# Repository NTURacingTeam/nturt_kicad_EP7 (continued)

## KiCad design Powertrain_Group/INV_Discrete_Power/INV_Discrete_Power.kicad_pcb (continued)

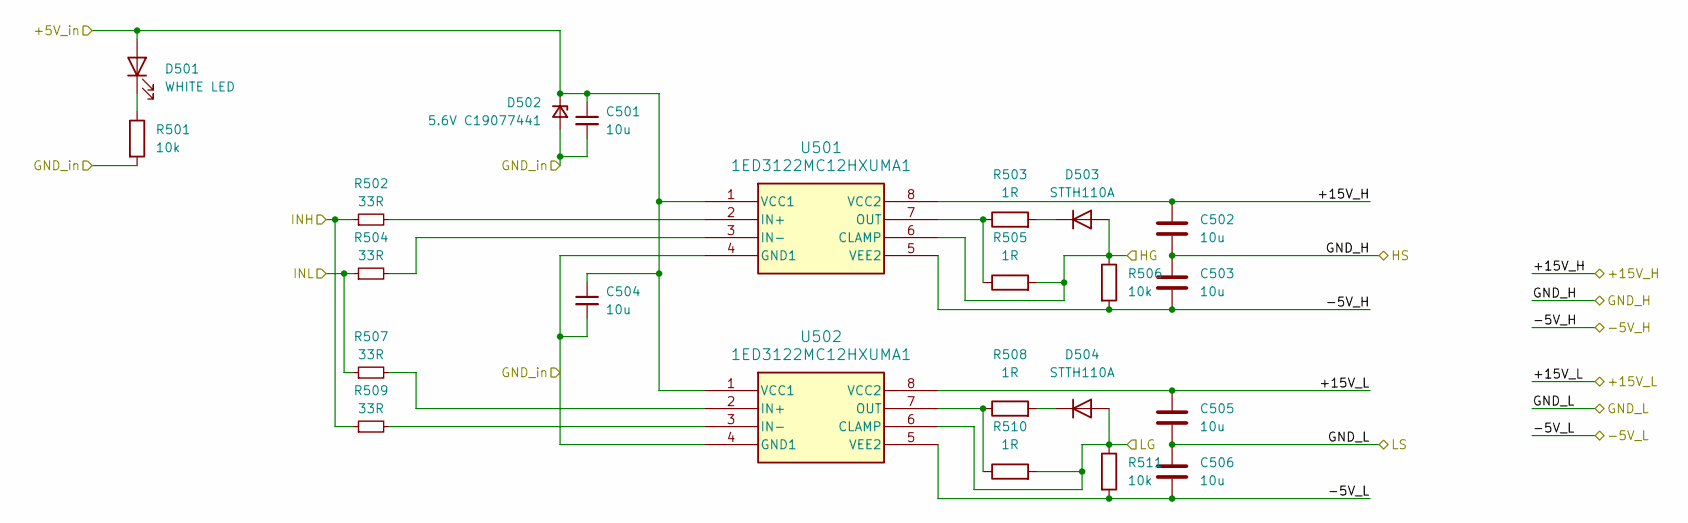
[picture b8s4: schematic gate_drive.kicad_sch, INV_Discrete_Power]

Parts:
C501, C502, C503, C504, C505, C506: 10u; C_0805_2012Metric
D501: WHITE LED; LED_0603_1608Metric
D502: 5.6V C19077441; D_SOD-323
D503, D504: STTH110A; D_SMA
R501: 10k; R_0402_1005Metric
R502, R504, R507, R509: 33R; R_0402_1005Metric
R503, R505, R508, R510: 1R; R_1206_3216Metric
R506, R511: 10k; R_0603_1608Metric
U501, U502: 1ED3122MC12HXUMA1; Infineon_PG-DSO-8-59_7.5x6.3mm

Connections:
/phaseW/PWR_+5V: C501.1, C504.1, D501.2 (A), D502.1 (K), U501.1 (VCC1), U502.1 (VCC1); also elsewhere on the board
/phaseW/PWR_GND: C501.2, C504.2, D502.2 (A), R501.2, U501.4 (GND1), U502.4 (GND1); also elsewhere on the board
/phaseW/gate_drive/+15V_H: C502.1, U501.8 (VCC2); also elsewhere on the board
/phaseW/gate_drive/+15V_L: C505.1, U502.8 (VCC2); also elsewhere on the board
/phaseW/gate_drive/-5V_H: C503.2, R506.2, U501.5 (VEE2); also elsewhere on the board
/phaseW/gate_drive/-5V_L: C506.2, R511.2, U502.5 (VEE2); also elsewhere on the board
/phaseW/gate_drive/GND_H: C502.2, C503.1; also elsewhere on the board
/phaseW/gate_drive/GND_L: C505.2, C506.1; also elsewhere on the board
/phaseW/gate_drive/HG: D503.2 (A), R505.2, R506.1, U501.6 (CLAMP); also elsewhere on the board
/phaseW/gate_drive/INH: R502.1, R509.1; also elsewhere on the board
/phaseW/gate_drive/INL: R504.1, R507.1; also elsewhere on the board
/phaseW/gate_drive/LG: D504.2 (A), R510.2, R511.1, U502.6 (CLAMP); also elsewhere on the board
unnamed: D501.1 (K), R501.1
unnamed: D503.1 (K), R503.2
unnamed: D504.1 (K), R508.2
unnamed: R502.2, U501.2 (IN+)
unnamed: R504.2, U501.3 (IN-)
unnamed: R503.1, R505.1, U501.7 (OUT)
unnamed: R507.2, U502.2 (IN+)
unnamed: R509.2, U502.3 (IN-)
unnamed: R508.1, R510.1, U502.7 (OUT)

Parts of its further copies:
C701, C702, C703, C704, C705, C706, C901, C902, C903, C904, C905, C906: 10u; C_0805_2012Metric
D701, D901: WHITE LED; LED_0603_1608Metric
D702, D902: 5.6V C19077441; D_SOD-323
D703, D704, D903, D904: STTH110A; D_SMA
R701, R901: 10k; R_0402_1005Metric
R702, R704, R707, R709, R902, R904, R907, R909: 33R; R_0402_1005Metric
R703, R705, R708, R710, R903, R905, R908, R910: 1R; R_1206_3216Metric
R706, R711, R906, R911: 10k; R_0603_1608Metric
U701, U702, U901, U902: 1ED3122MC12HXUMA1; Infineon_PG-DSO-8-59_7.5x6.3mm

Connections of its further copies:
/phaseU/PWR_+5V: C901.1, C904.1, D901.2 (A), D902.1 (K), U901.1 (VCC1), U902.1 (VCC1); also elsewhere on the board
/phaseU/PWR_GND: C901.2, C904.2, D902.2 (A), R901.2, U901.4 (GND1), U902.4 (GND1); also elsewhere on the board
/phaseU/gate_drive/+15V_H: C902.1, U901.8 (VCC2); also elsewhere on the board
/phaseU/gate_drive/+15V_L: C905.1, U902.8 (VCC2); also elsewhere on the board
/phaseU/gate_drive/-5V_H: C903.2, R906.2, U901.5 (VEE2); also elsewhere on the board
/phaseU/gate_drive/-5V_L: C906.2, R911.2, U902.5 (VEE2); also elsewhere on the board
/phaseU/gate_drive/GND_H: C902.2, C903.1; also elsewhere on the board
/phaseU/gate_drive/GND_L: C905.2, C906.1; also elsewhere on the board
/phaseU/gate_drive/HG: D903.2 (A), R905.2, R906.1, U901.6 (CLAMP); also elsewhere on the board
/phaseU/gate_drive/INH: R902.1, R909.1; also elsewhere on the board
/phaseU/gate_drive/INL: R904.1, R907.1; also elsewhere on the board
/phaseU/gate_drive/LG: D904.2 (A), R910.2, R911.1, U902.6 (CLAMP); also elsewhere on the board
/phaseV/PWR_+5V: C701.1, C704.1, D701.2 (A), D702.1 (K), U701.1 (VCC1), U702.1 (VCC1); also elsewhere on the board
/phaseV/PWR_GND: C701.2, C704.2, D702.2 (A), R701.2, U701.4 (GND1), U702.4 (GND1); also elsewhere on the board
/phaseV/gate_drive/+15V_H: C702.1, U701.8 (VCC2); also elsewhere on the board
/phaseV/gate_drive/+15V_L: C705.1, U702.8 (VCC2); also elsewhere on the board
/phaseV/gate_drive/-5V_H: C703.2, R706.2, U701.5 (VEE2); also elsewhere on the board
/phaseV/gate_drive/-5V_L: C706.2, R711.2, U702.5 (VEE2); also elsewhere on the board
/phaseV/gate_drive/GND_H: C702.2, C703.1; also elsewhere on the board
/phaseV/gate_drive/GND_L: C705.2, C706.1; also elsewhere on the board
/phaseV/gate_drive/HG: D703.2 (A), R705.2, R706.1, U701.6 (CLAMP); also elsewhere on the board
/phaseV/gate_drive/INH: R702.1, R709.1; also elsewhere on the board
/phaseV/gate_drive/INL: R704.1, R707.1; also elsewhere on the board
/phaseV/gate_drive/LG: D704.2 (A), R710.2, R711.1, U702.6 (CLAMP); also elsewhere on the board
unnamed: D701.1 (K), R701.1
unnamed: D703.1 (K), R703.2
unnamed: D704.1 (K), R708.2
unnamed: D901.1 (K), R901.1
unnamed: D903.1 (K), R903.2
unnamed: D904.1 (K), R908.2
unnamed: R702.2, U701.2 (IN+)
unnamed: R704.2, U701.3 (IN-)
unnamed: R703.1, R705.1, U701.7 (OUT)
unnamed: R707.2, U702.2 (IN+)
unnamed: R709.2, U702.3 (IN-)
unnamed: R708.1, R710.1, U702.7 (OUT)
unnamed: R902.2, U901.2 (IN+)
unnamed: R904.2, U901.3 (IN-)
unnamed: R903.1, R905.1, U901.7 (OUT)
unnamed: R907.2, U902.2 (IN+)
unnamed: R909.2, U902.3 (IN-)
unnamed: R908.1, R910.1, U902.7 (OUT)

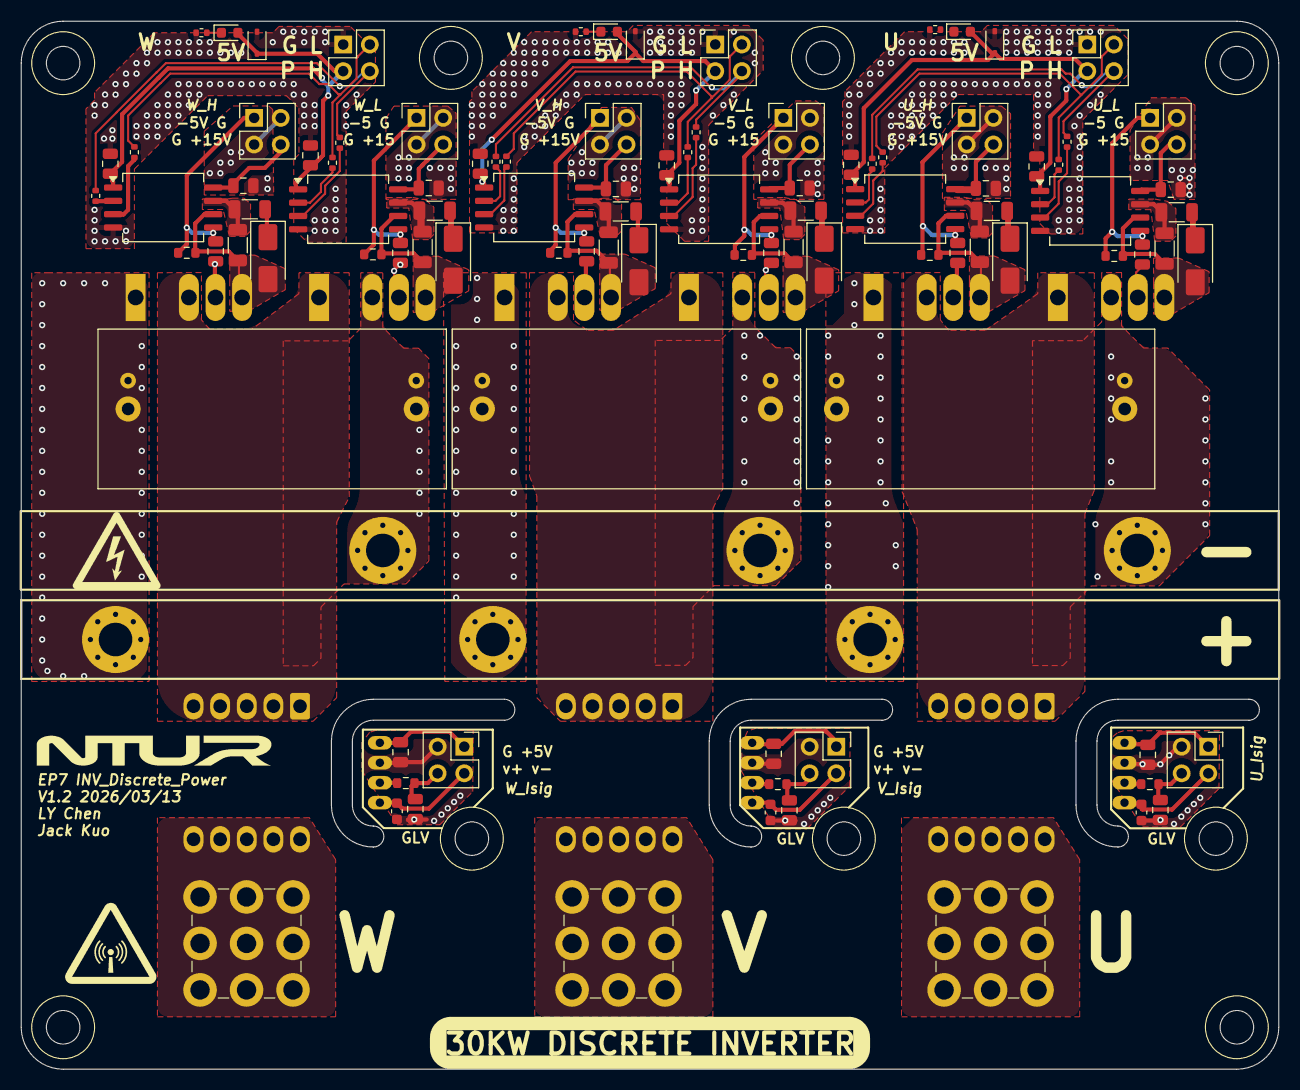
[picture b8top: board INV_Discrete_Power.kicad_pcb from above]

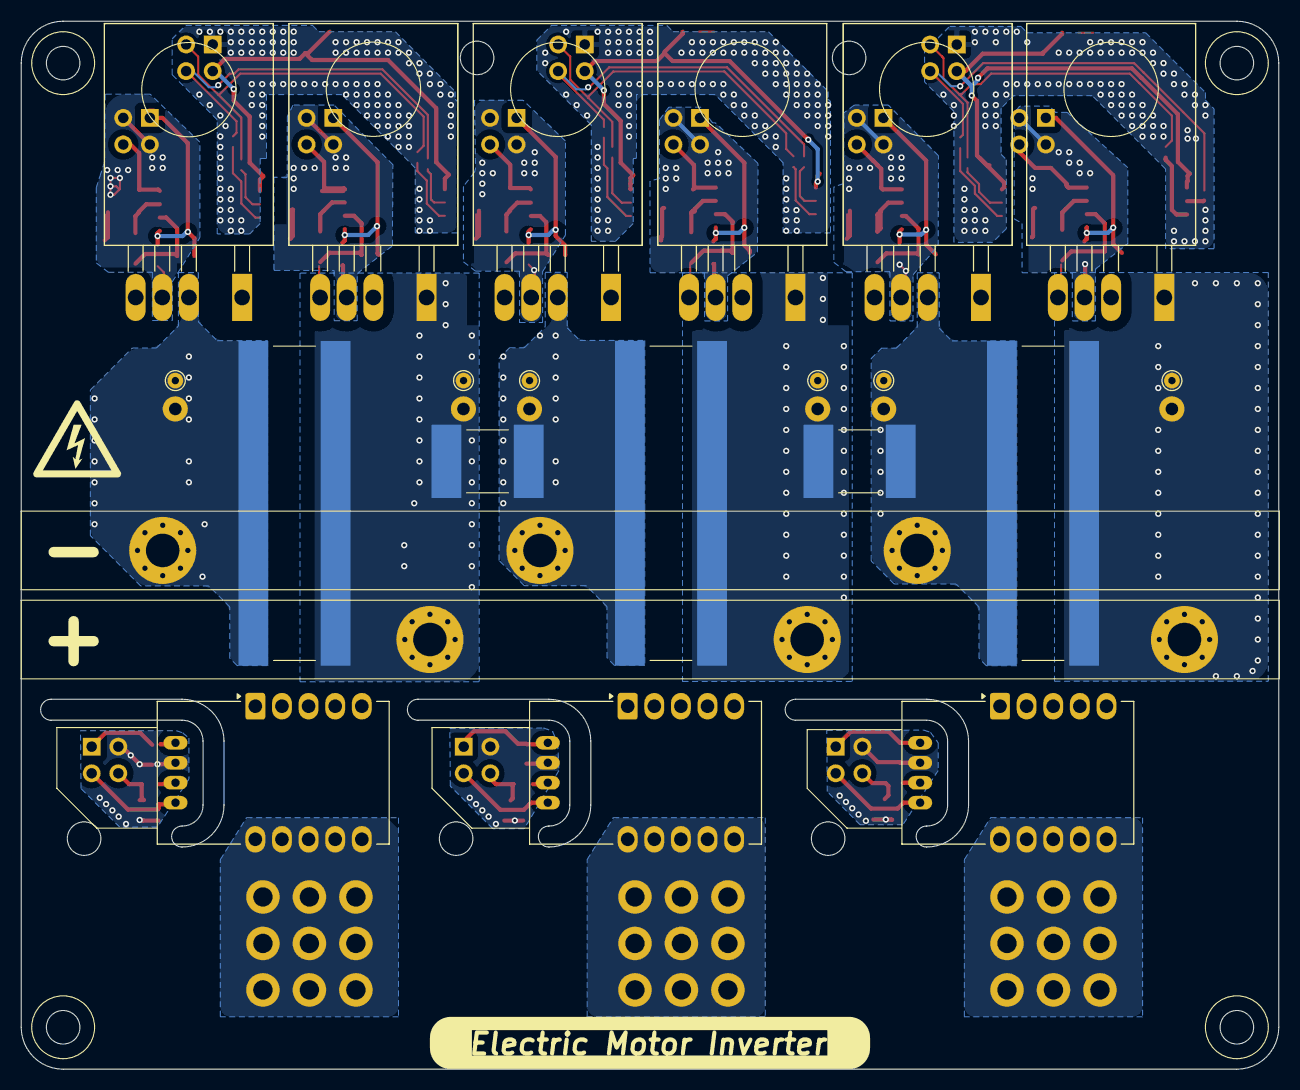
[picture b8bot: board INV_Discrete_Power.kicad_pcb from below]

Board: 2 copper layers, 120.0 x 100.0 mm, 134 parts (20 on the bottom side), 90 nets.
